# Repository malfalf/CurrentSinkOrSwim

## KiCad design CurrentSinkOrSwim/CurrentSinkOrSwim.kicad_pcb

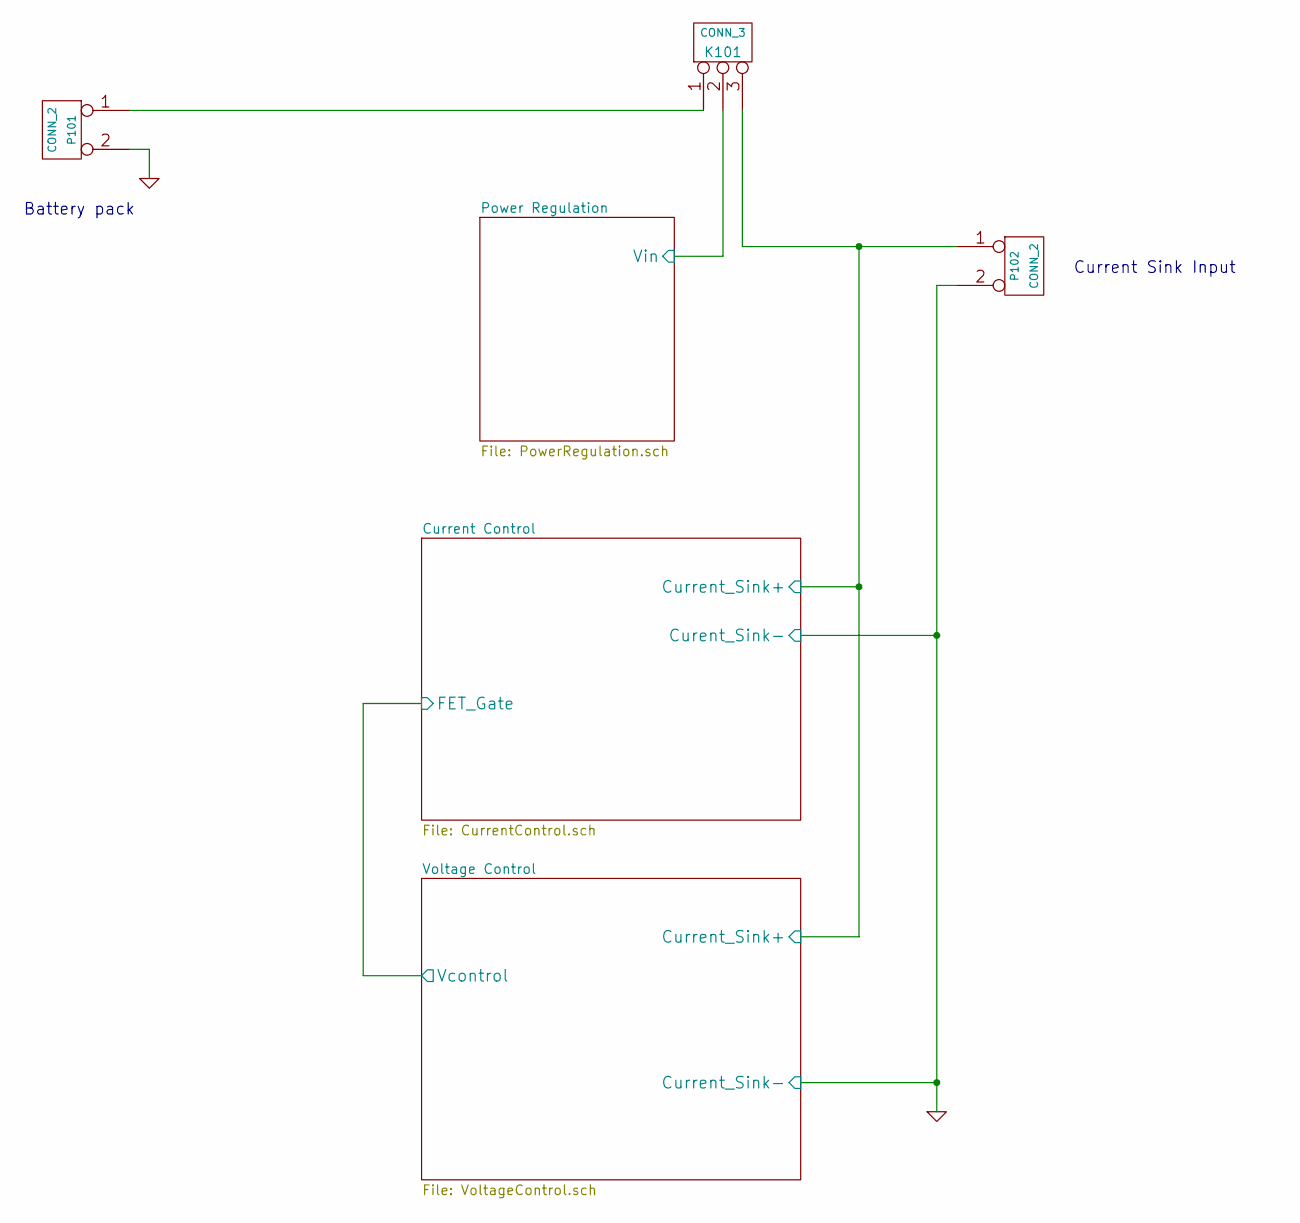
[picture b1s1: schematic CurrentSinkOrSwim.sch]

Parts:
K101: CONN_3
P101, P102: CONN_2

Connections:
/Current Control/Current_Sink+: K101.3, P102.1; also elsewhere on the board
/Power Regulation/Vin: K101.2 (PM); also elsewhere on the board
GND: P101.2 (PM), P102.2 (PM); also elsewhere on the board
unnamed: K101.1, P101.1

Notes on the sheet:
Current Sink Input
Battery pack

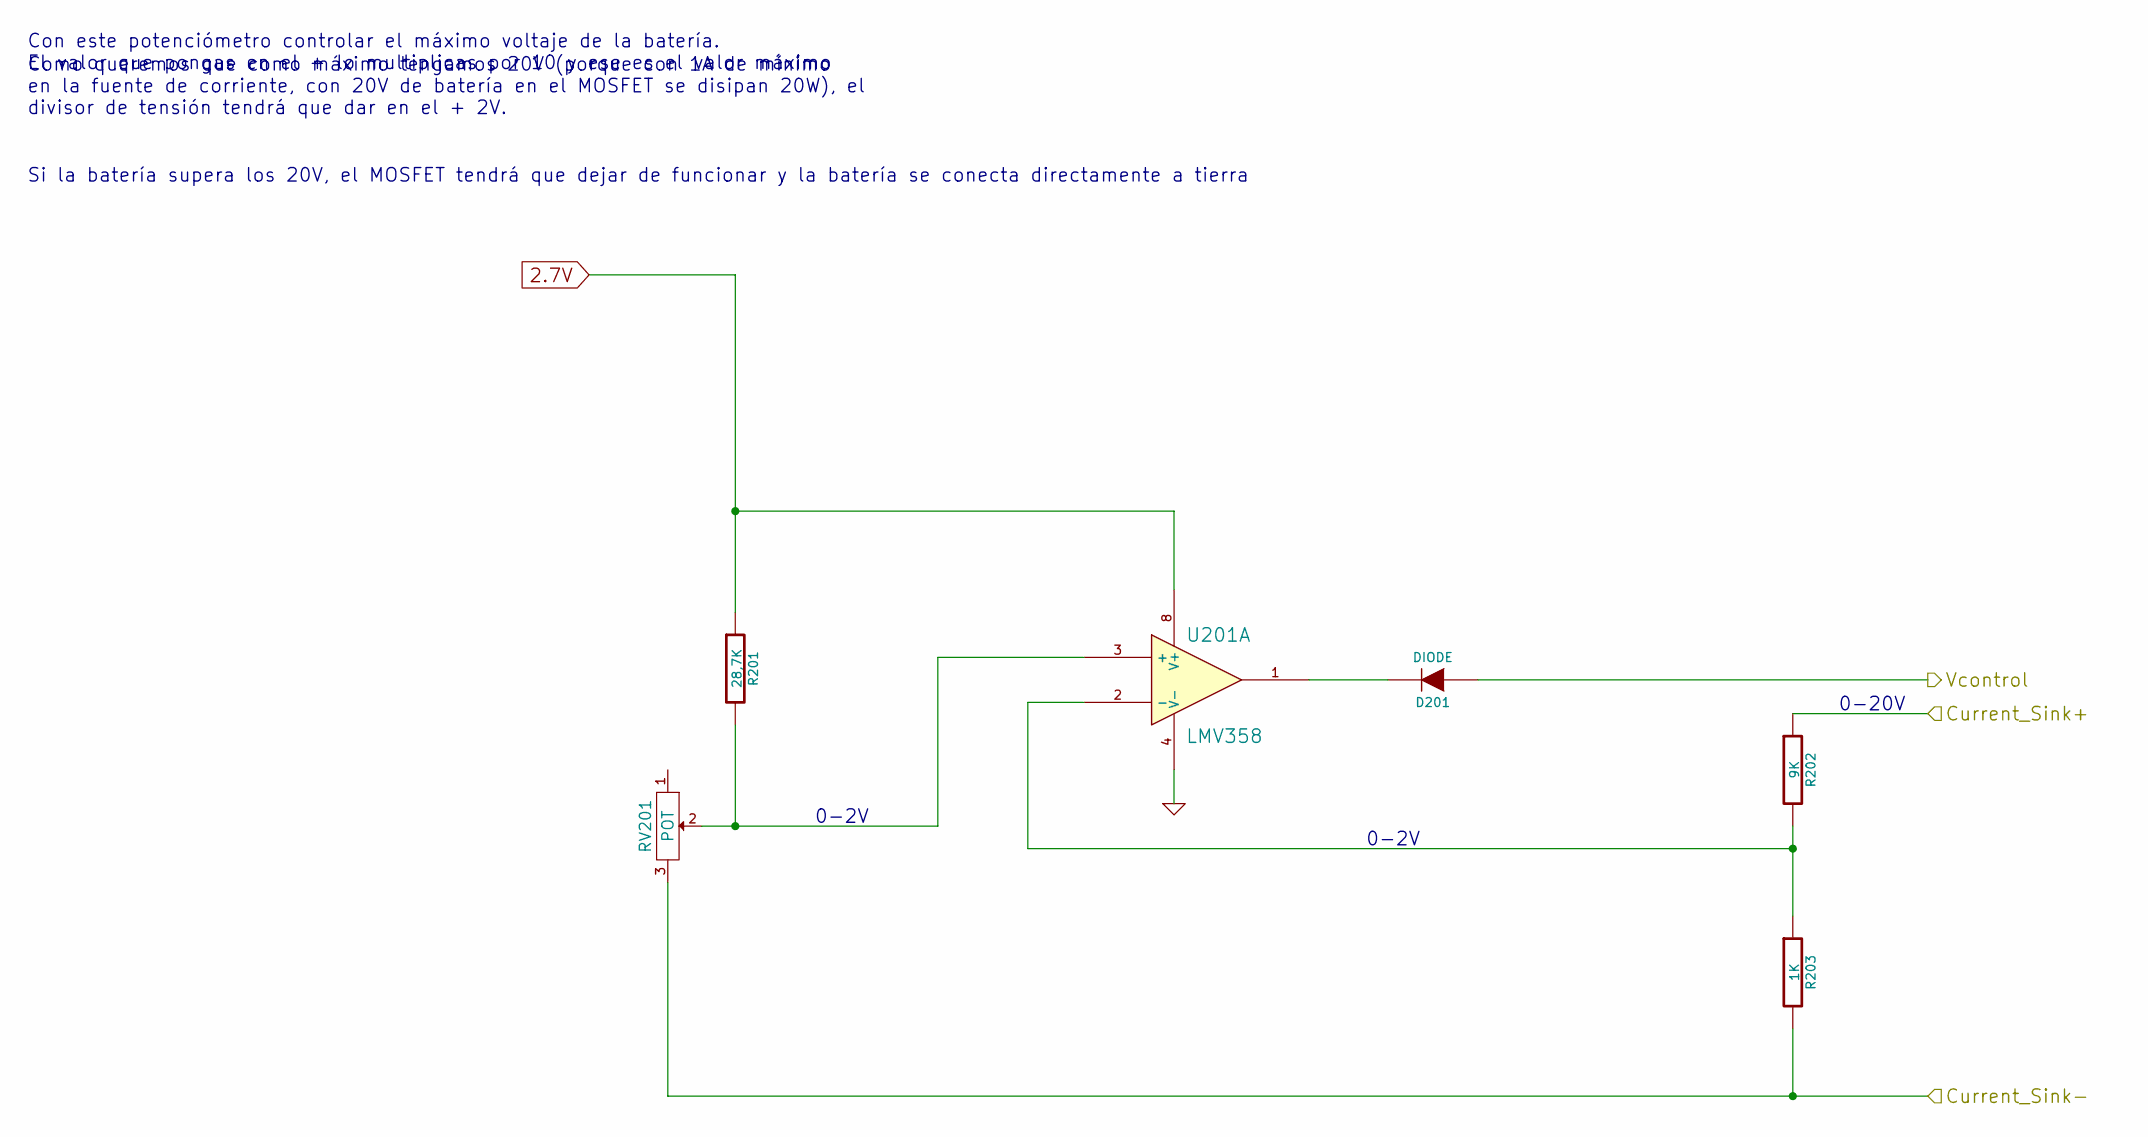
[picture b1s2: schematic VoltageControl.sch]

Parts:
D201: DIODE
R201: 28,7K
R202: 9K
R203: 1K
RV201: POT
U201: LMV358

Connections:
2.7V: R201.1, U201.8 (V+); also elsewhere on the board
/Current Control/Current_Sink+: R202.1; also elsewhere on the board
/Current Control/FET_Gate: D201.1 (A); also elsewhere on the board
GND: R203.2, RV201.3, U201.4 (V-); also elsewhere on the board
unnamed: R202.2, R203.1, U201.2 (-)
unnamed: D201.2 (K), U201.1
unnamed: R201.2, RV201.2, U201.3 (+)

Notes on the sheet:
Con este potenciómetro controlar el máximo voltaje de la batería. El valor que pongas en el + lo multiplicas por 10 y ese es el valor máximo
Como queremos que como máximo tengamos 20V (porque con 1A de mínimo en la fuente de corriente, con 20V de batería en el MOSFET se disipan 20W), el divisor de tensión tendrá que dar en el + 2V.
Si la batería supera los 20V, el MOSFET tendrá que dejar de funcionar y la batería se conecta directamente a tierra
0-2V
0-20V

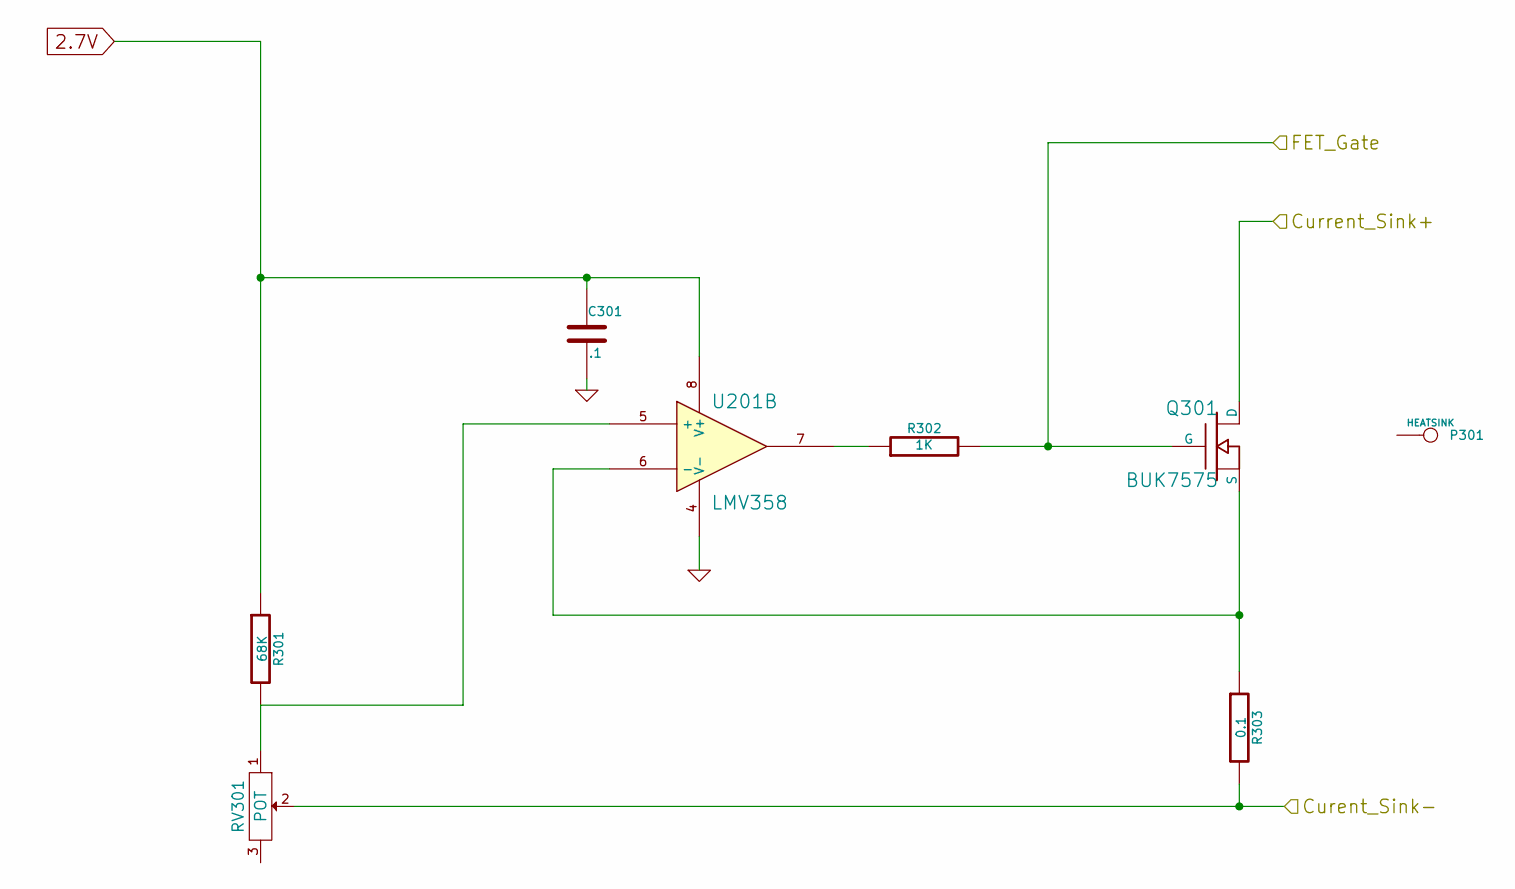
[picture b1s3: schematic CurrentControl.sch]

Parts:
C301: .1
P301: HEATSINK
Q301: BUK7575; MFG Part Number BUK7575-100A
R301: 68K
R302: 1K
R303: 0.1; MFG Part Number LVR01R1000FE12
RV301: POT
U201: LMV358

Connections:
2.7V: C301.1, R301.1, U201.8 (V+); also elsewhere on the board
/Current Control/Current_Sink+: Q301.D; also elsewhere on the board
/Current Control/FET_Gate: Q301.G, R302.2; also elsewhere on the board
GND: C301.2, R303.2, RV301.2, U201.4 (V-); also elsewhere on the board
unnamed: R302.1, U201.7
unnamed: R301.2, RV301.1, U201.5 (+)
unnamed: Q301.S, R303.1, U201.6 (-)

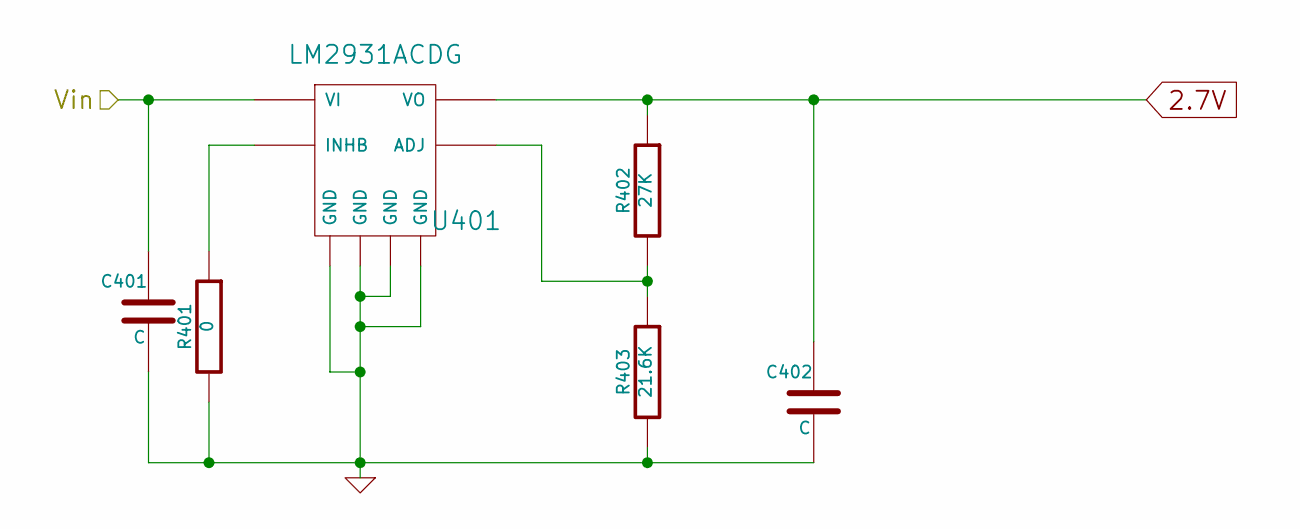
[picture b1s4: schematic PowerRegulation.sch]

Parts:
C401, C402: C
R401: 0
R402: 27K
R403: 21.6K
U401: LM2931ACDG

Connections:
2.7V: C402.1, R402.1, U401.1 (VO); also elsewhere on the board
/Power Regulation/Vin: C401.1, U401.8 (VI); also elsewhere on the board
GND: C401.2, C402.2, R401.2, R403.2, U401.2 (GND), U401.3 (GND), U401.6 (GND), U401.7 (GND); also elsewhere on the board
unnamed: R401.1, U401.5 (INHB)
unnamed: R402.2, R403.1, U401.4 (ADJ)

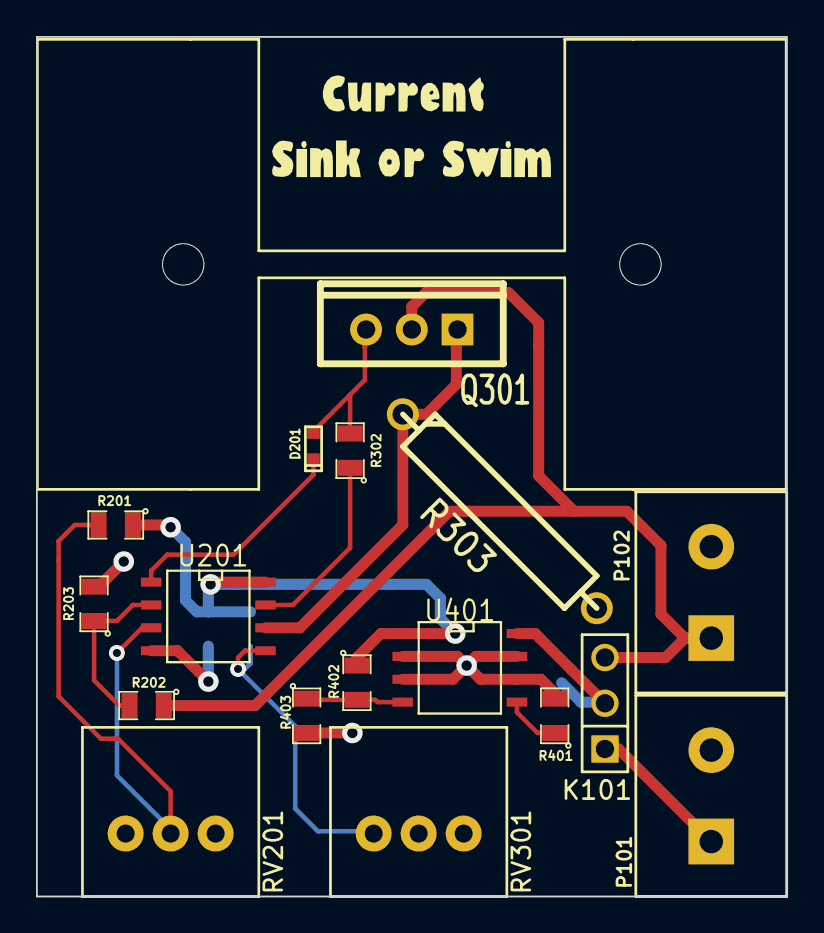
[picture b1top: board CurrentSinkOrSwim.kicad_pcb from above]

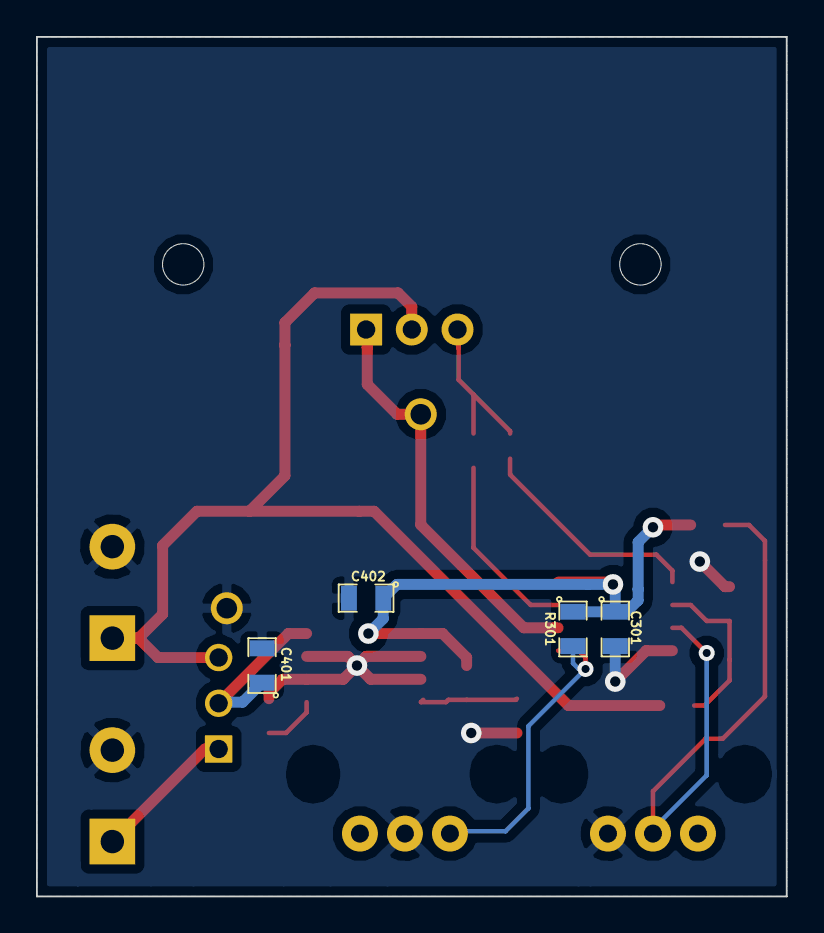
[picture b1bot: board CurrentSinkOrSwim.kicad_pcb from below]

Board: 2 copper layers, 41.7 x 47.8 mm, 22 parts (4 on the bottom side), 14 nets.

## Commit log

2015-08-21 KiCad project and schematic creation
2015-08-21 Adding preliminary components (without values) to the schematic
2015-09-01 Modificado el esquemático (cambiando el LDO)
2015-09-01 Subo los archivos de simulación LTSpice
2015-09-01 adding new sheets
2015-09-06 Schematic annotate
2015-09-06 Cambios en la simulación
2015-09-06 Añadiendo net list, footprints y nombres a los componentes que no lo tenían. Empezando con el layout
2015-09-09 creado footprint heatsink
2015-09-19 Cambiados footprints del potenciometro
2015-09-19 cambiando potenciómetro y divisores de tension
2015-09-19 placing components in the PCB
2015-09-21 first layout session
2015-09-24 Layout session 2
2015-09-26 Design Rule Check
2015-09-26 generando los ficheros Gerber y metiendo el logo
2015-09-26 Creados de nuevo los ficheros Gerber, cambiando alguna línea de los footprints de los potenciómetros y fusionando en un único documento el gerber de los taladros para que lo reconozco OSHpark
2015-10-01 Actualizando información de los componentes y creando el BOM
2015-10-06 Haciendo algunos cambios porque he tenido que cambiar de componentes y algún valor estaba mal
